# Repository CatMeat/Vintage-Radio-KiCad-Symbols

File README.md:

# Vintage-Radio-KiCad-Symbols
Vacuum tube and passive components most commonly found in pre-transistor radios.

Primary goal is to create a set of symbol libraries that cover 99% of the components 
found in older tube radios such as the All American Fives (AA5) and others. The libraries 
should contain common items, even if already present in other standard libraries. Reduce 
the choices to create effeciency.

## This is a work in progress
No guarantees are made for usability. These symbols were drawn in KiCad 8.0 and later.

## Design notes
- All symbols should be drawn on 50.00 mils grid (Kicad default for all symbols).
- All pins/connections must fall on this grid.

## See individual library README's for more information specific to that library.

---

Looking for collaborators, contact me. K4TFJ, good on QRZ and here.

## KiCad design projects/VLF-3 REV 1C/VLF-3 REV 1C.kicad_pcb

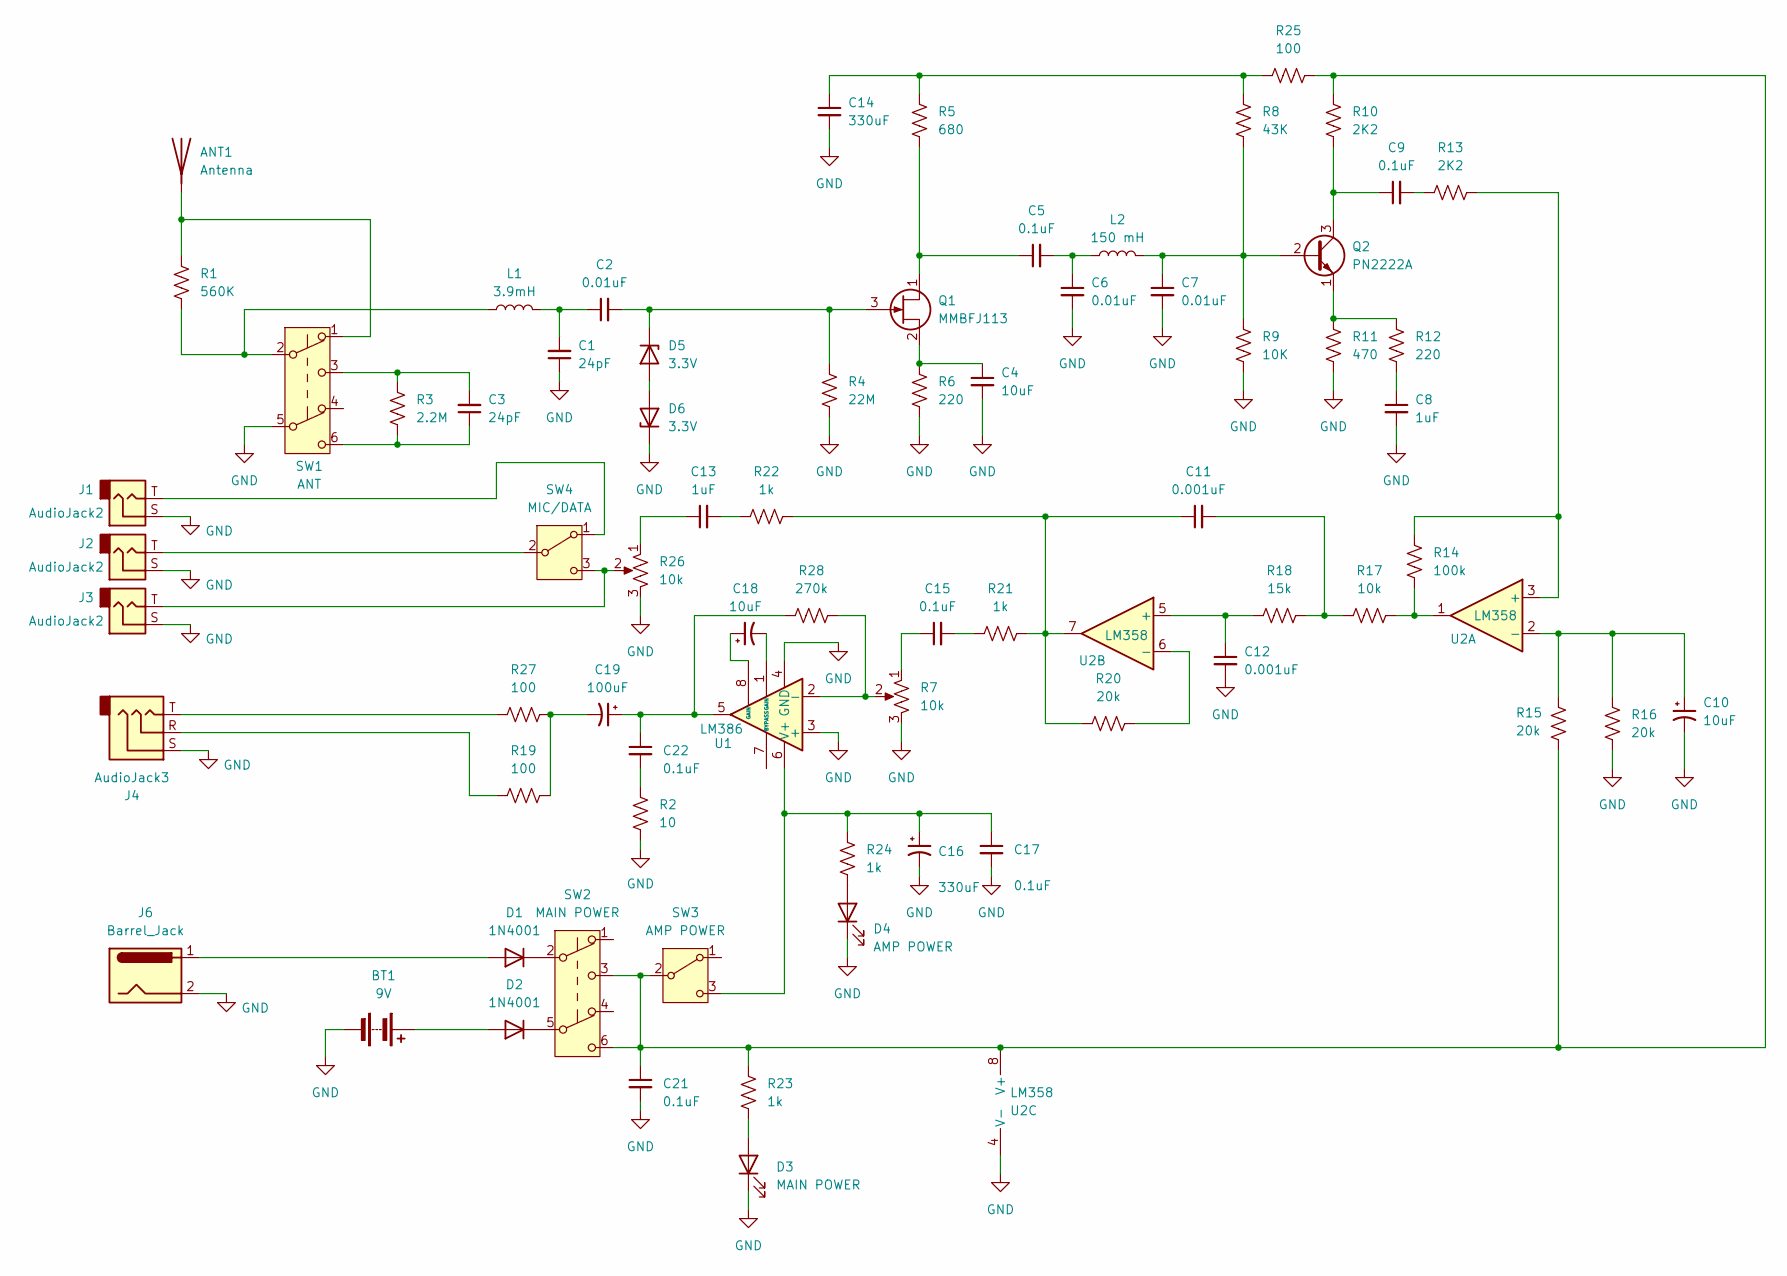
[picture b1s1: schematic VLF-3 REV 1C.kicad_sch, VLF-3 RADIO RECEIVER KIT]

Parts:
ANT1: Antenna; BNC_Amphenol_031-6575_Horizontal
BT1: 9V
C1, C3: 24pF; C_Disc_D6.0mm_W2.5mm_P5.00mm
C2, C6, C7: 0.01uF; C_Disc_D6.0mm_W2.5mm_P5.00mm
C4, C10: 10uF; C_Disc_D6.0mm_W2.5mm_P5.00mm
C5, C9, C15, C17, C21, C22: 0.1uF; C_Disc_D6.0mm_W2.5mm_P5.00mm
C8, C13: 1uF; C_Disc_D6.0mm_W2.5mm_P5.00mm
C11, C12: 0.001uF; C_Disc_D6.0mm_W2.5mm_P5.00mm
C14, C16: 330uF; CP_Radial_D5.0mm_P2.50mm
C18: 10uF; CP_Radial_D5.0mm_P2.50mm
C19: 100uF; CP_Radial_D5.0mm_P2.50mm
D1, D2: 1N4001; D_DO-41_SOD81_P10.16mm_Horizontal
D3: MAIN POWER; LED_D3.0mm
D4: AMP POWER; LED_D3.0mm
D5, D6: 3.3V; D_A-405_P7.62mm_Horizontal
J1, J2, J3: AudioJack2; Jack_3.5mm_CUI_SJ1-3533NG_Horizontal_CircularHoles
J4: AudioJack3; Jack_3.5mm_PJ320D_Horizontal
J6: Barrel_Jack; BarrelJack_CUI_PJ-063AH_Horizontal_CircularHoles
L1: 3.9mH; L_Axial_L6.6mm_D2.7mm_P10.16mm_Horizontal_Vishay_IM-2
L2: 150 mH; L_Axial_L6.6mm_D2.7mm_P10.16mm_Horizontal_Vishay_IM-2
Q1: MMBFJ113; SOT-23
Q2: PN2222A; TO-92_Inline
R1: 560K; R_Axial_DIN0204_L3.6mm_D1.6mm_P7.62mm_Horizontal
R2: 10; R_Axial_DIN0204_L3.6mm_D1.6mm_P7.62mm_Horizontal
R3: 2.2M; R_Axial_DIN0204_L3.6mm_D1.6mm_P7.62mm_Horizontal
R4: 22M; R_Axial_DIN0204_L3.6mm_D1.6mm_P7.62mm_Horizontal
R5: 680; R_Axial_DIN0204_L3.6mm_D1.6mm_P7.62mm_Horizontal
R6, R12: 220; R_Axial_DIN0204_L3.6mm_D1.6mm_P7.62mm_Horizontal
R7, R26: 10k; Potentiometer_Alps_RK163_Single_Horizontal
R8: 43K; R_Axial_DIN0204_L3.6mm_D1.6mm_P7.62mm_Horizontal
R9: 10K; R_Axial_DIN0204_L3.6mm_D1.6mm_P7.62mm_Horizontal
R10, R13: 2K2; R_Axial_DIN0204_L3.6mm_D1.6mm_P7.62mm_Horizontal
R11: 470; R_Axial_DIN0204_L3.6mm_D1.6mm_P7.62mm_Horizontal
R14: 100k; R_Axial_DIN0204_L3.6mm_D1.6mm_P7.62mm_Horizontal
R15, R16, R20: 20k; R_Axial_DIN0204_L3.6mm_D1.6mm_P7.62mm_Horizontal
R17: 10k; R_Axial_DIN0204_L3.6mm_D1.6mm_P7.62mm_Horizontal
R18: 15k; R_Axial_DIN0204_L3.6mm_D1.6mm_P7.62mm_Horizontal
R19, R25, R27: 100; R_Axial_DIN0204_L3.6mm_D1.6mm_P7.62mm_Horizontal
R21, R22, R23, R24: 1k; R_Axial_DIN0204_L3.6mm_D1.6mm_P7.62mm_Horizontal
R28: 270k; R_Axial_DIN0204_L3.6mm_D1.6mm_P7.62mm_Horizontal
SW1: ANT; SW_Push_2P2T_Toggle_CK_PVA2OAH5xxxxxxV2
SW2: MAIN POWER; SW_Push_2P2T_Toggle_CK_PVA2OAH5xxxxxxV2
SW3: AMP POWER; SW_E-Switch_EG1271_SPDT
SW4: MIC/DATA; SW_E-Switch_EG1271_SPDT
U1: LM386; DIP-8-16_W7.62mm_Socket_LongPads
U2: LM358; DIP-8-16_W7.62mm_Socket_LongPads

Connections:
GND: BT1.2 (-), C1.1, C4.2, C6.2, C7.2, C8.2, C10.2, C12.2, C14.2, C16.2, C17.2, C21.2, D3.1 (K), D4.1 (K), D6.1 (K), J1.S, J2.S, J3.S, J4.S, J6.2, R2.1, R4.2, R6.2, R7.3, R9.2, R11.2, R16.2, R26.3, SW1.5 (B), U1.3 (+), U1.4 (GND), U2.4 (V-)
unnamed: ANT1.1 (A), R1.1, SW1.1 (A)
unnamed: BT1.1 (+), D2.2 (A)
unnamed: C1.2, C2.1, L1.2
unnamed: C3.1, R3.2, SW1.6 (C)
unnamed: C3.2, R3.1, SW1.3 (C)
unnamed: C5.2, C6.1, L2.1
unnamed: C8.1, R12.2
unnamed: C9.2, R13.1
unnamed: C11.1, R20.1, R21.2, R22.2, U2.7
unnamed: C11.2, R17.1, R18.2
unnamed: C13.1, R26.1
unnamed: C13.2, R22.1
unnamed: C14.1, R5.1, R8.1, R25.2
unnamed: C15.1, R7.1
unnamed: C15.2, R21.1
unnamed: C18.1, U1.8 (GAIN)
unnamed: C18.2, U1.1 (GAIN)
unnamed: C19.1, C22.1, R28.1, U1.5
unnamed: C19.2, R19.2, R27.2
unnamed: C22.2, R2.2
unnamed: D1.2 (A), J6.1
unnamed: D1.1 (K), SW2.2 (B)
unnamed: D2.1 (K), SW2.5 (B)
unnamed: D3.2 (A), R23.1
unnamed: D4.2 (A), R24.1
unnamed: D5.2 (A), D6.2 (A)
unnamed: C2.2, D5.1 (K), Q1.3 (G), R4.1
unnamed: J4.R, R19.1
unnamed: J4.T, R27.1
unnamed: L1.1, R1.2, SW1.2 (B)
unnamed: C5.1, Q1.1 (D), R5.2
unnamed: C4.1, Q1.2 (S), R6.1
unnamed: C7.1, L2.2, Q2.2 (B), R8.2, R9.1
unnamed: C9.1, Q2.3 (C), R10.2
unnamed: Q2.1 (E), R11.1, R12.1
unnamed: R14.2, R17.2, U2.1
unnamed: C21.1, R10.1, R15.2, R23.2, R25.1, SW2.3 (C), SW2.6 (C), SW3.2 (B), U2.8 (V+)
unnamed: C16.1, C17.1, R24.2, SW3.3 (C), U1.6 (V+)
unnamed: J1.T, SW4.1 (A)
unnamed: J2.T, SW4.2 (B)
unnamed: J3.T, R26.2, SW4.3 (C)
unnamed: R7.2, R28.2, U1.2 (-)
unnamed: R13.2, R14.1, U2.3 (+)
unnamed: C10.1, R15.1, R16.1, U2.2 (-)
unnamed: C12.1, R18.1, U2.5 (+)
unnamed: R20.2, U2.6 (-)

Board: 2 copper layers, 71 parts (0 on the bottom side), 45 nets, no tracks yet.

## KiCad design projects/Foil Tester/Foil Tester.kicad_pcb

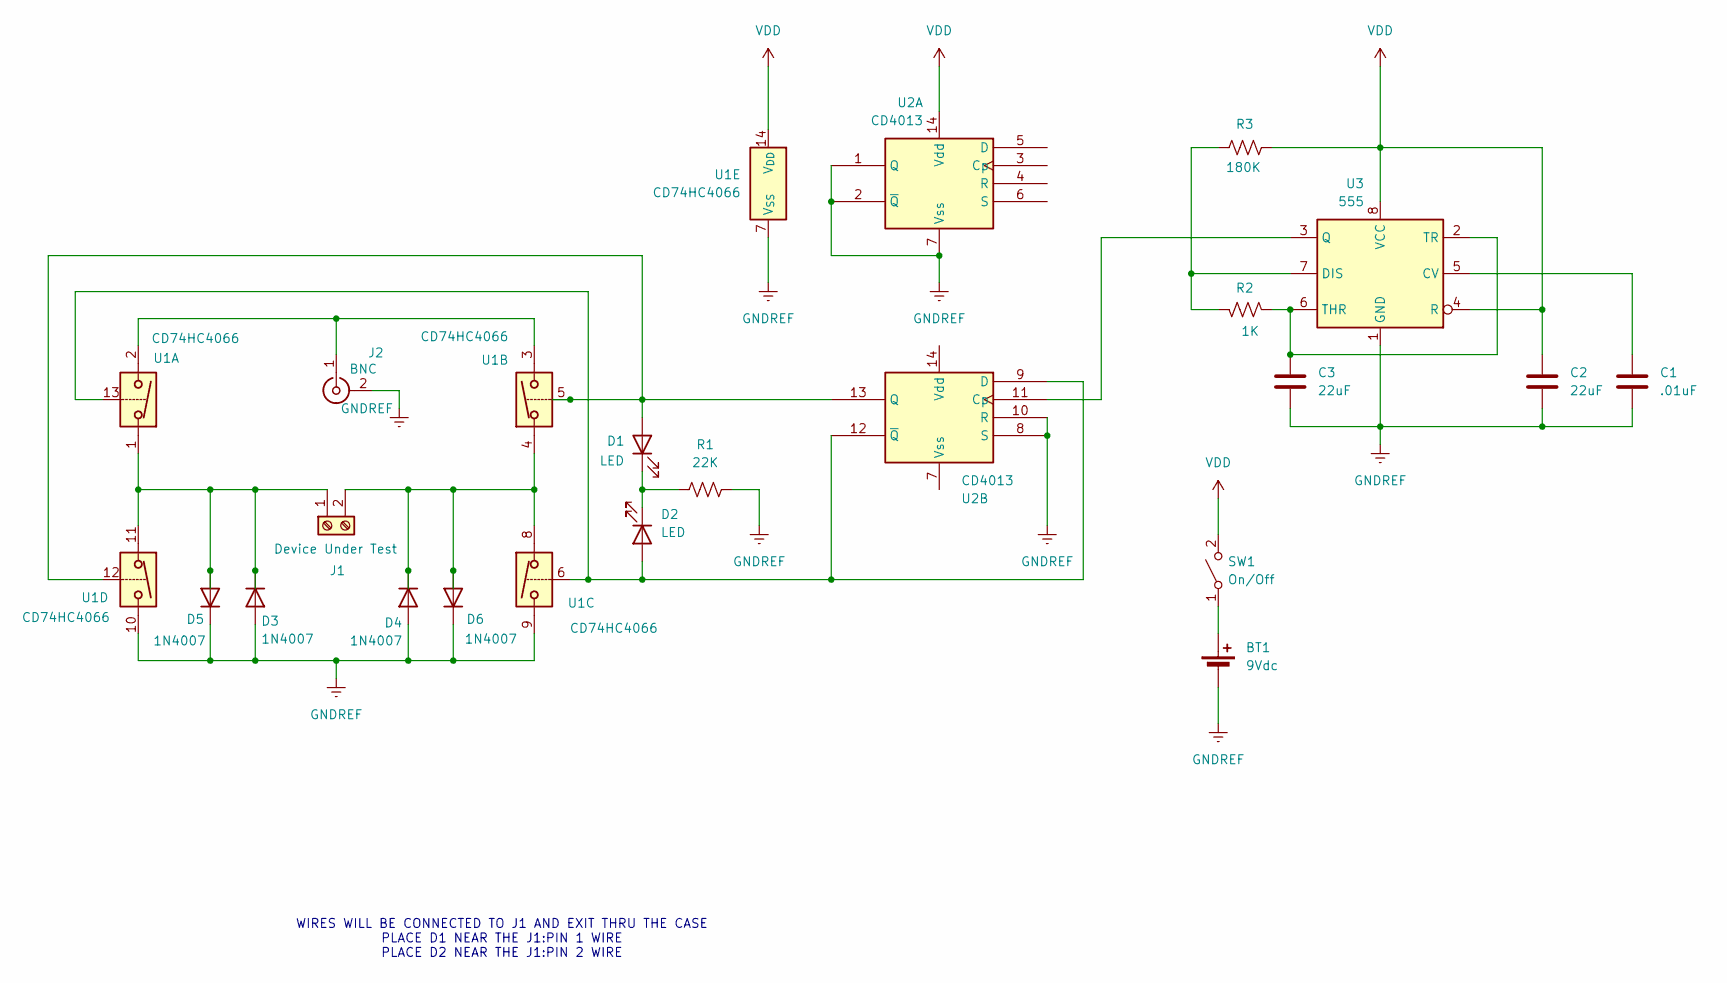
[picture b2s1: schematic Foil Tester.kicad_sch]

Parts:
BT1: 9Vdc; R_Axial_DIN0204_L3.6mm_D1.6mm_P7.62mm_Horizontal
C1: .01uF; C_Radial_D5.0mm_H11.0mm_P2.00mm
C2, C3: 22uF; C_Radial_D5.0mm_H11.0mm_P2.00mm
D1, D2: LED; D_A-405_P7.62mm_Horizontal
D3, D4, D5, D6: 1N4007; D_DO-41_SOD81_P10.16mm_Horizontal
J1: Device Under Test; TerminalBlock_bornier-2_P5.08mm
J2: BNC; BNC_Amphenol_B6252HB-NPP3G-50_Horizontal
R1: 22K; R_Axial_DIN0204_L3.6mm_D1.6mm_P7.62mm_Horizontal
R2: 1K; R_Axial_DIN0204_L3.6mm_D1.6mm_P7.62mm_Horizontal
R3: 180K; R_Axial_DIN0204_L3.6mm_D1.6mm_P7.62mm_Horizontal
SW1: On/Off; R_Axial_DIN0204_L3.6mm_D1.6mm_P7.62mm_Horizontal
U1: CD74HC4066; DIP-14_W7.62mm
U2: CD4013; DIP-14_W7.62mm
U3: 555; DIP-8_W7.62mm

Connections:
GNDREF: BT1.2 (-), C1.2, C2.2, C3.2, D3.2 (A), D4.2 (A), D5.1 (K), D6.1 (K), J2.2 (Ext), R1.2, U1.7 (V_{SS}), U1.9, U1.10, U2.1 (Q), U2.2 (~Q), U2.7 (Vss), U2.8 (S), U2.10 (R), U3.1 (GND)
unnamed: BT1.1 (+), SW1.1 (A)
unnamed: D1.2 (A), U1.5, U1.12, U2.13 (Q)
unnamed: D1.1 (K), D2.1 (K), R1.1
unnamed: D2.2 (A), U1.6, U1.13, U2.9 (D), U2.12 (~Q)
unnamed: D3.1 (K), D5.2 (A), J1.1, U1.1, U1.11
unnamed: D4.1 (K), D6.2 (A), J1.2, U1.4, U1.8
unnamed: J2.1 (In), U1.2, U1.3
unnamed: U2.11 (Cp), U3.3 (Q)
unnamed: C1.1, U3.5 (CV)
unnamed: R2.1, R3.1, U3.7 (DIS)
unnamed: C3.1, R2.2, U3.2 (TR), U3.6 (THR)
VDD: C2.1, R3.2, SW1.2 (B), U1.14 (V_{DD}), U2.14 (Vdd), U3.4 (R), U3.8 (VCC)

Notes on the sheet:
WIRES WILL BE CONNECTED TO J1 AND EXIT THRU THE CASE PLACE D1 NEAR THE J1:PIN 1 WIRE PLACE D2 NEAR THE J1:PIN 2 WIRE

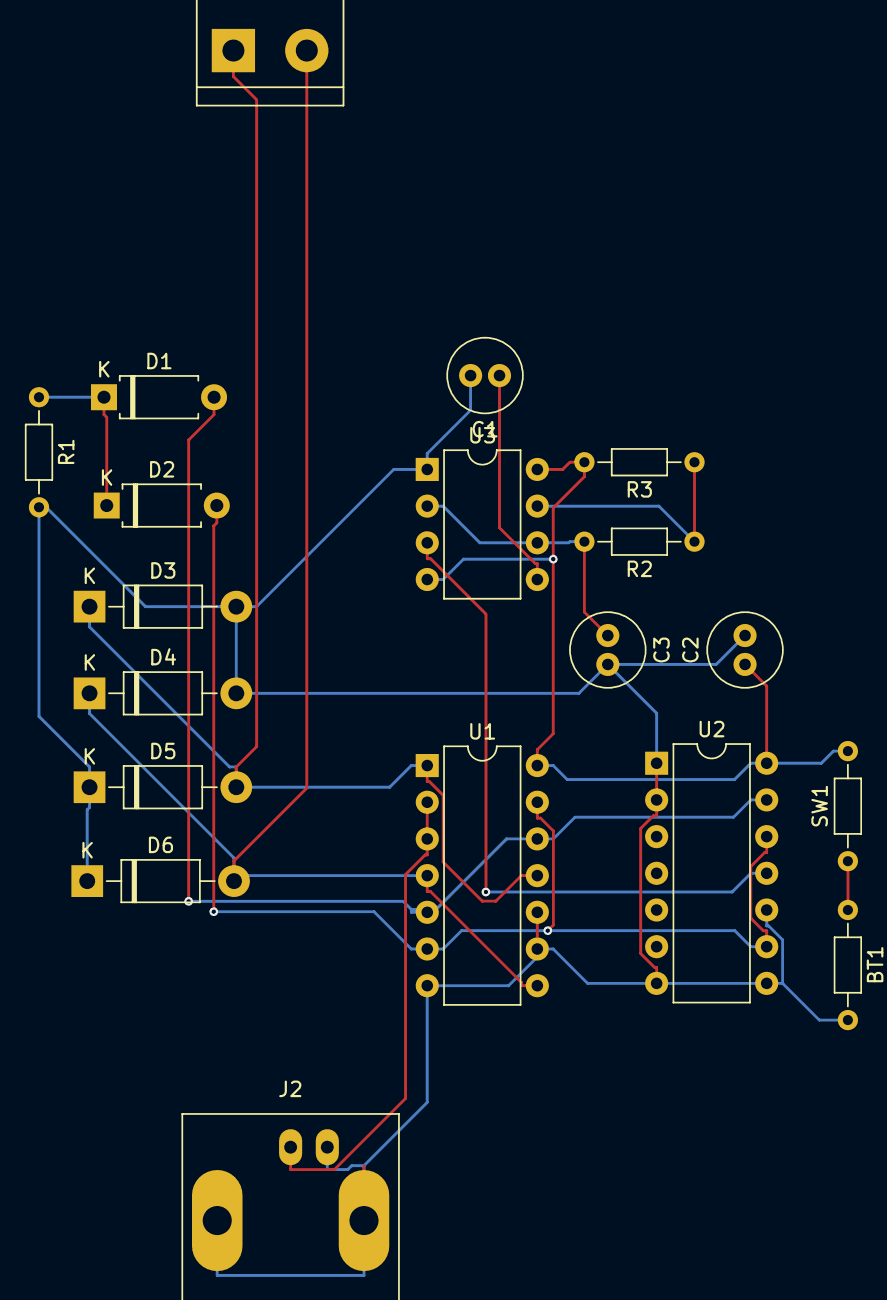
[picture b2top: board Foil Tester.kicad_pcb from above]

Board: 2 copper layers, 19 parts (0 on the bottom side), 13 nets.

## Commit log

2025-03-18 Update README.md
    Initialization of readme.
2025-03-18 Create test
2025-03-18 separate into folders
2025-03-18 more readme changes
2025-03-18 Create Octal Socket.kicad_mod
    Begin adding footprints
2025-03-18 Update Vintage_Radio_Vacuum_Tubes.kicad_sym
    added 6DQ6B
2025-03-18 add octal template
2025-03-18 misc changes
    misc changes
2025-03-19 6BE6 changes
2025-03-19 Footprint changes
2025-03-24 add LAMP and HEATER
2025-03-24 add projects
2025-03-25 LOTS OF ADDS
2025-03-25 MORE CHANGES
2025-03-25 MULTIPLE VALUE CHANGES
